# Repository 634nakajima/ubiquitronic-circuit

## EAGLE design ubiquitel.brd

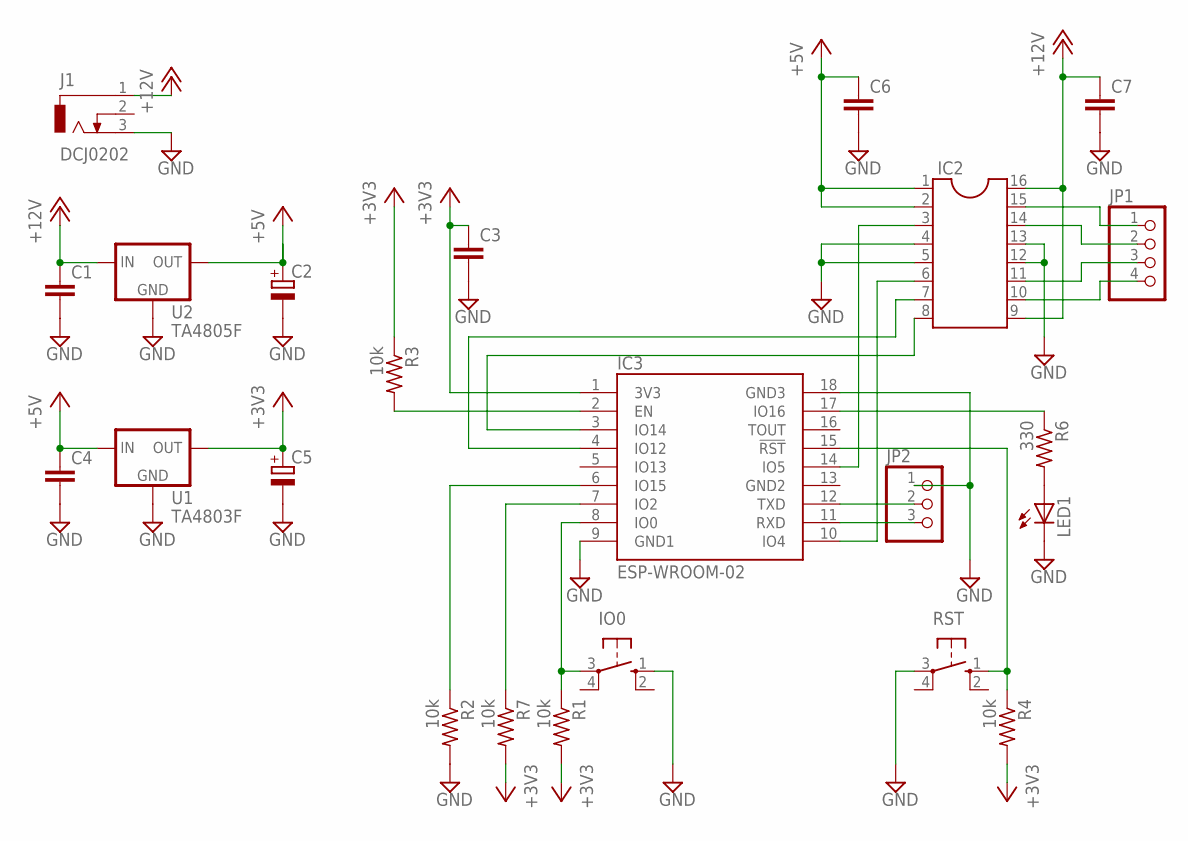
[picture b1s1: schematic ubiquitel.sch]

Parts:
C1, C3, C4, C6, C7: C-EU025-024X044; C025-024X044
C2, C5: CPOL-EUE2-5; E2-5
IC2: DIL16S; SOCKET-16
IC3: ESP-WROOM-02; WROOM-02
IO0: 10-XX(タクトスイッチ); B3F-10XX
J1: DCJ0202
JP1: PINHD-1X4; 1X04
JP2: PINHD-1X3; 1X03
LED1: LED3MM
R1, R2, R3, R4, R7: 10k; 0207/10
R6: 330; 0207/10
RST: 10-XX(タクトスイッチ); B3F-10XX
U1: TA4803F; CUSTOM
U2: TA4805F; CUSTOM

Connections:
+3V3: C3.1, C5.+, IC3.1 (3V3), R1.2, R3.1, R4.2, R7.2, U1.P$3 (OUT)
+5V: C2.+, C4.1, C6.1, IC2.1, IC2.2, U1.P$1 (IN), U2.P$3 (OUT)
+12V: C1.1, C7.1, IC2.9, IC2.16, J1.1, U2.P$1 (IN)
GND: C1.2, C2.-, C3.2, C4.2, C5.-, C6.2, C7.2, IC2.4, IC2.5, IC2.12, IC2.13, IC3.9 (GND1), IC3.18 (GND3), IO0.1 (S), J1.3, JP2.1, LED1.K (C), R2.2, RST.3, U1.P$2 (GND), U2.P$2 (GND)
unnamed: IC3.6 (IO15), R2.1
unnamed: IC3.2 (EN), R3.2
unnamed: IC3.11 (RXD), JP2.3
unnamed: IC3.15 (!RST!), R4.1, RST.1 (S)
unnamed: IC3.7 (IO2), R7.1
unnamed: IC2.3, IC3.14 (IO5)
unnamed: IC2.6, IC3.10 (IO4)
unnamed: IC2.7, IC3.4 (IO12)
unnamed: IC2.8, IC3.3 (IO14)
unnamed: IC3.8 (IO0), IO0.3, R1.1
unnamed: LED1.A, R6.2
unnamed: IC3.17 (IO16), R6.1
unnamed: IC3.12 (TXD), JP2.2
unnamed: IC2.10, JP1.4
unnamed: IC2.11, JP1.3
unnamed: IC2.14, JP1.2
unnamed: IC2.15, JP1.1

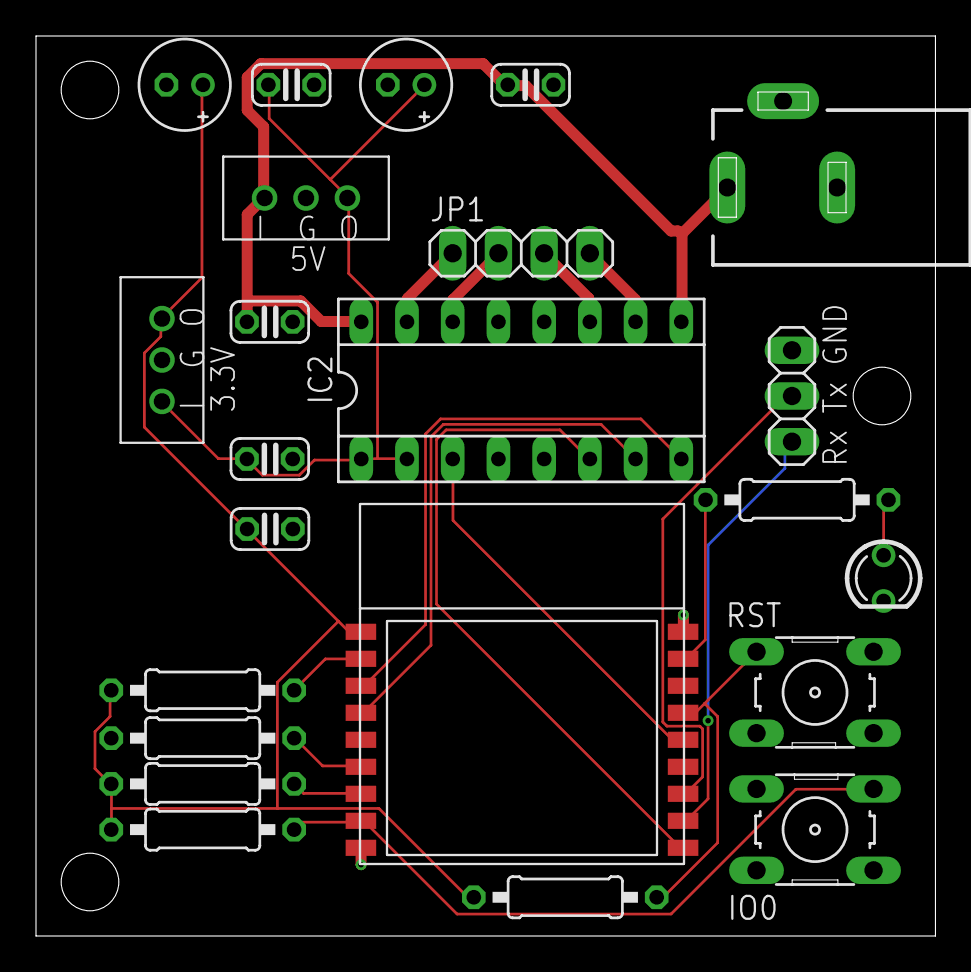
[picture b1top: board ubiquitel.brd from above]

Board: 2 copper layers, 50.0 x 50.0 mm, 23 parts (0 on the bottom side), 21 nets.

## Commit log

2018-03-10 setup
2018-11-03 add screen printing
